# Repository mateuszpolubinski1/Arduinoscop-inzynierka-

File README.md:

# ArduinoScope – Modular Educational Measurement Device
*A universal, low-cost measurement platform based on Raspberry Pi Pico*

---

## Overview
ArduinoScope is a **modular electronic measurement device** designed as an educational platform for electronics and metrology laboratories.  
The project was developed as an **engineering thesis** and combines **analog front-end design**, **ADC-based signal acquisition**, and **embedded software development**.

The device is built around the **Raspberry Pi Pico (RP2040)** microcontroller and can be reconfigured via software to operate as:
- Oscilloscope
- Spectrum analyzer
- Wobuloscope
- Vector voltmeter
- Frequency counter

---

## System Architecture
The system is based on a **modular architecture**, consisting of a mainboard and multiple plug-in expansion modules.

Key blocks of the system:
- Modular analog input boards
- Mainboard with Raspberry Pi Pico (RP2040)
- Internal ADC for signal acquisition
- TFT display with touchscreen
- USB interface for communication with a PC
- Dedicated power supply module

---

## Analog Front-End Design
Two independent analog input paths were designed to support different measurement scenarios.

### Differential Input Path

- Based on **INA2137 instrumentation amplifier**
- Fixed gain using precision, internally matched resistors
- High common-mode rejection (CMRR)
- Enables voltage measurement between any two points in a circuit
- Dedicated overvoltage protection to protect the ADC

---

### Single-Ended Input Path

- Based on **OPA1644 / TL084 operational amplifiers**
- Electronically adjustable gain
- Separate signal paths for DC and AC components
- Software-controlled signal conditioning similar to a classic oscilloscope
- Input and output protection for safe educational use

---

## Protection & Signal Conditioning
To ensure robustness and safe operation:
- Input protection using **BAV99-AQ diodes** (low leakage, low capacitance)
- ADC protection using **BAS40 Schottky diodes**
- Precision voltage references (**TL431**, **LM385**) for proper ADC range adaptation
- Designed to withstand accidental overvoltage conditions during laboratory exercises

---

## PCB Design
Custom printed circuit boards were designed using **KiCad**, with particular attention to analog signal integrity.

PCB design highlights:
- Modular plug-in boards connected via pin headers
- Noise-aware routing and ground plane usage
- Separation of analog and digital sections
- Easy manufacturing and repair

---

## Software
The firmware was developed using:
- **Arduino**
- **MicroPython**

Main software features:
- Data acquisition from internal ADC
- Signal processing and scaling
- User interface handling (display and touchscreen)
- USB communication for offline data transfer to PC

---

## Measurements & Validation
The device was validated through laboratory measurements.

Validation results:
- Correct operation within the acoustic frequency range
- Stable gain and offset control
- Proper operation of protection circuits
- Reliable signal acquisition using the RP2040 ADC

---

## User Interface
The built-in TFT display provides direct visualization of measured signals.

The user interface allows real-time interaction and configuration without the need for an external computer.

---

## Technologies Used
**Hardware**
- Raspberry Pi Pico (RP2040)
- INA2137, OPA1644, TL084
- AD9850 signal generator
- PCF8575 I/O expander

**Software & Tools**
- Arduino, MicroPython
- KiCad, LTspice
- Oscilloscope and laboratory measurement equipment

---

## Project Status & Future Work
Status:
- Fully functional prototype
- Successfully tested in laboratory conditions

Possible future improvements:
- External higher-resolution ADC
- Improved bandwidth and noise performance
- PC-based visualization and analysis software

---

## Author
**Mateusz Połubiński**  
Electronics Engineering – Warsaw University of Technology

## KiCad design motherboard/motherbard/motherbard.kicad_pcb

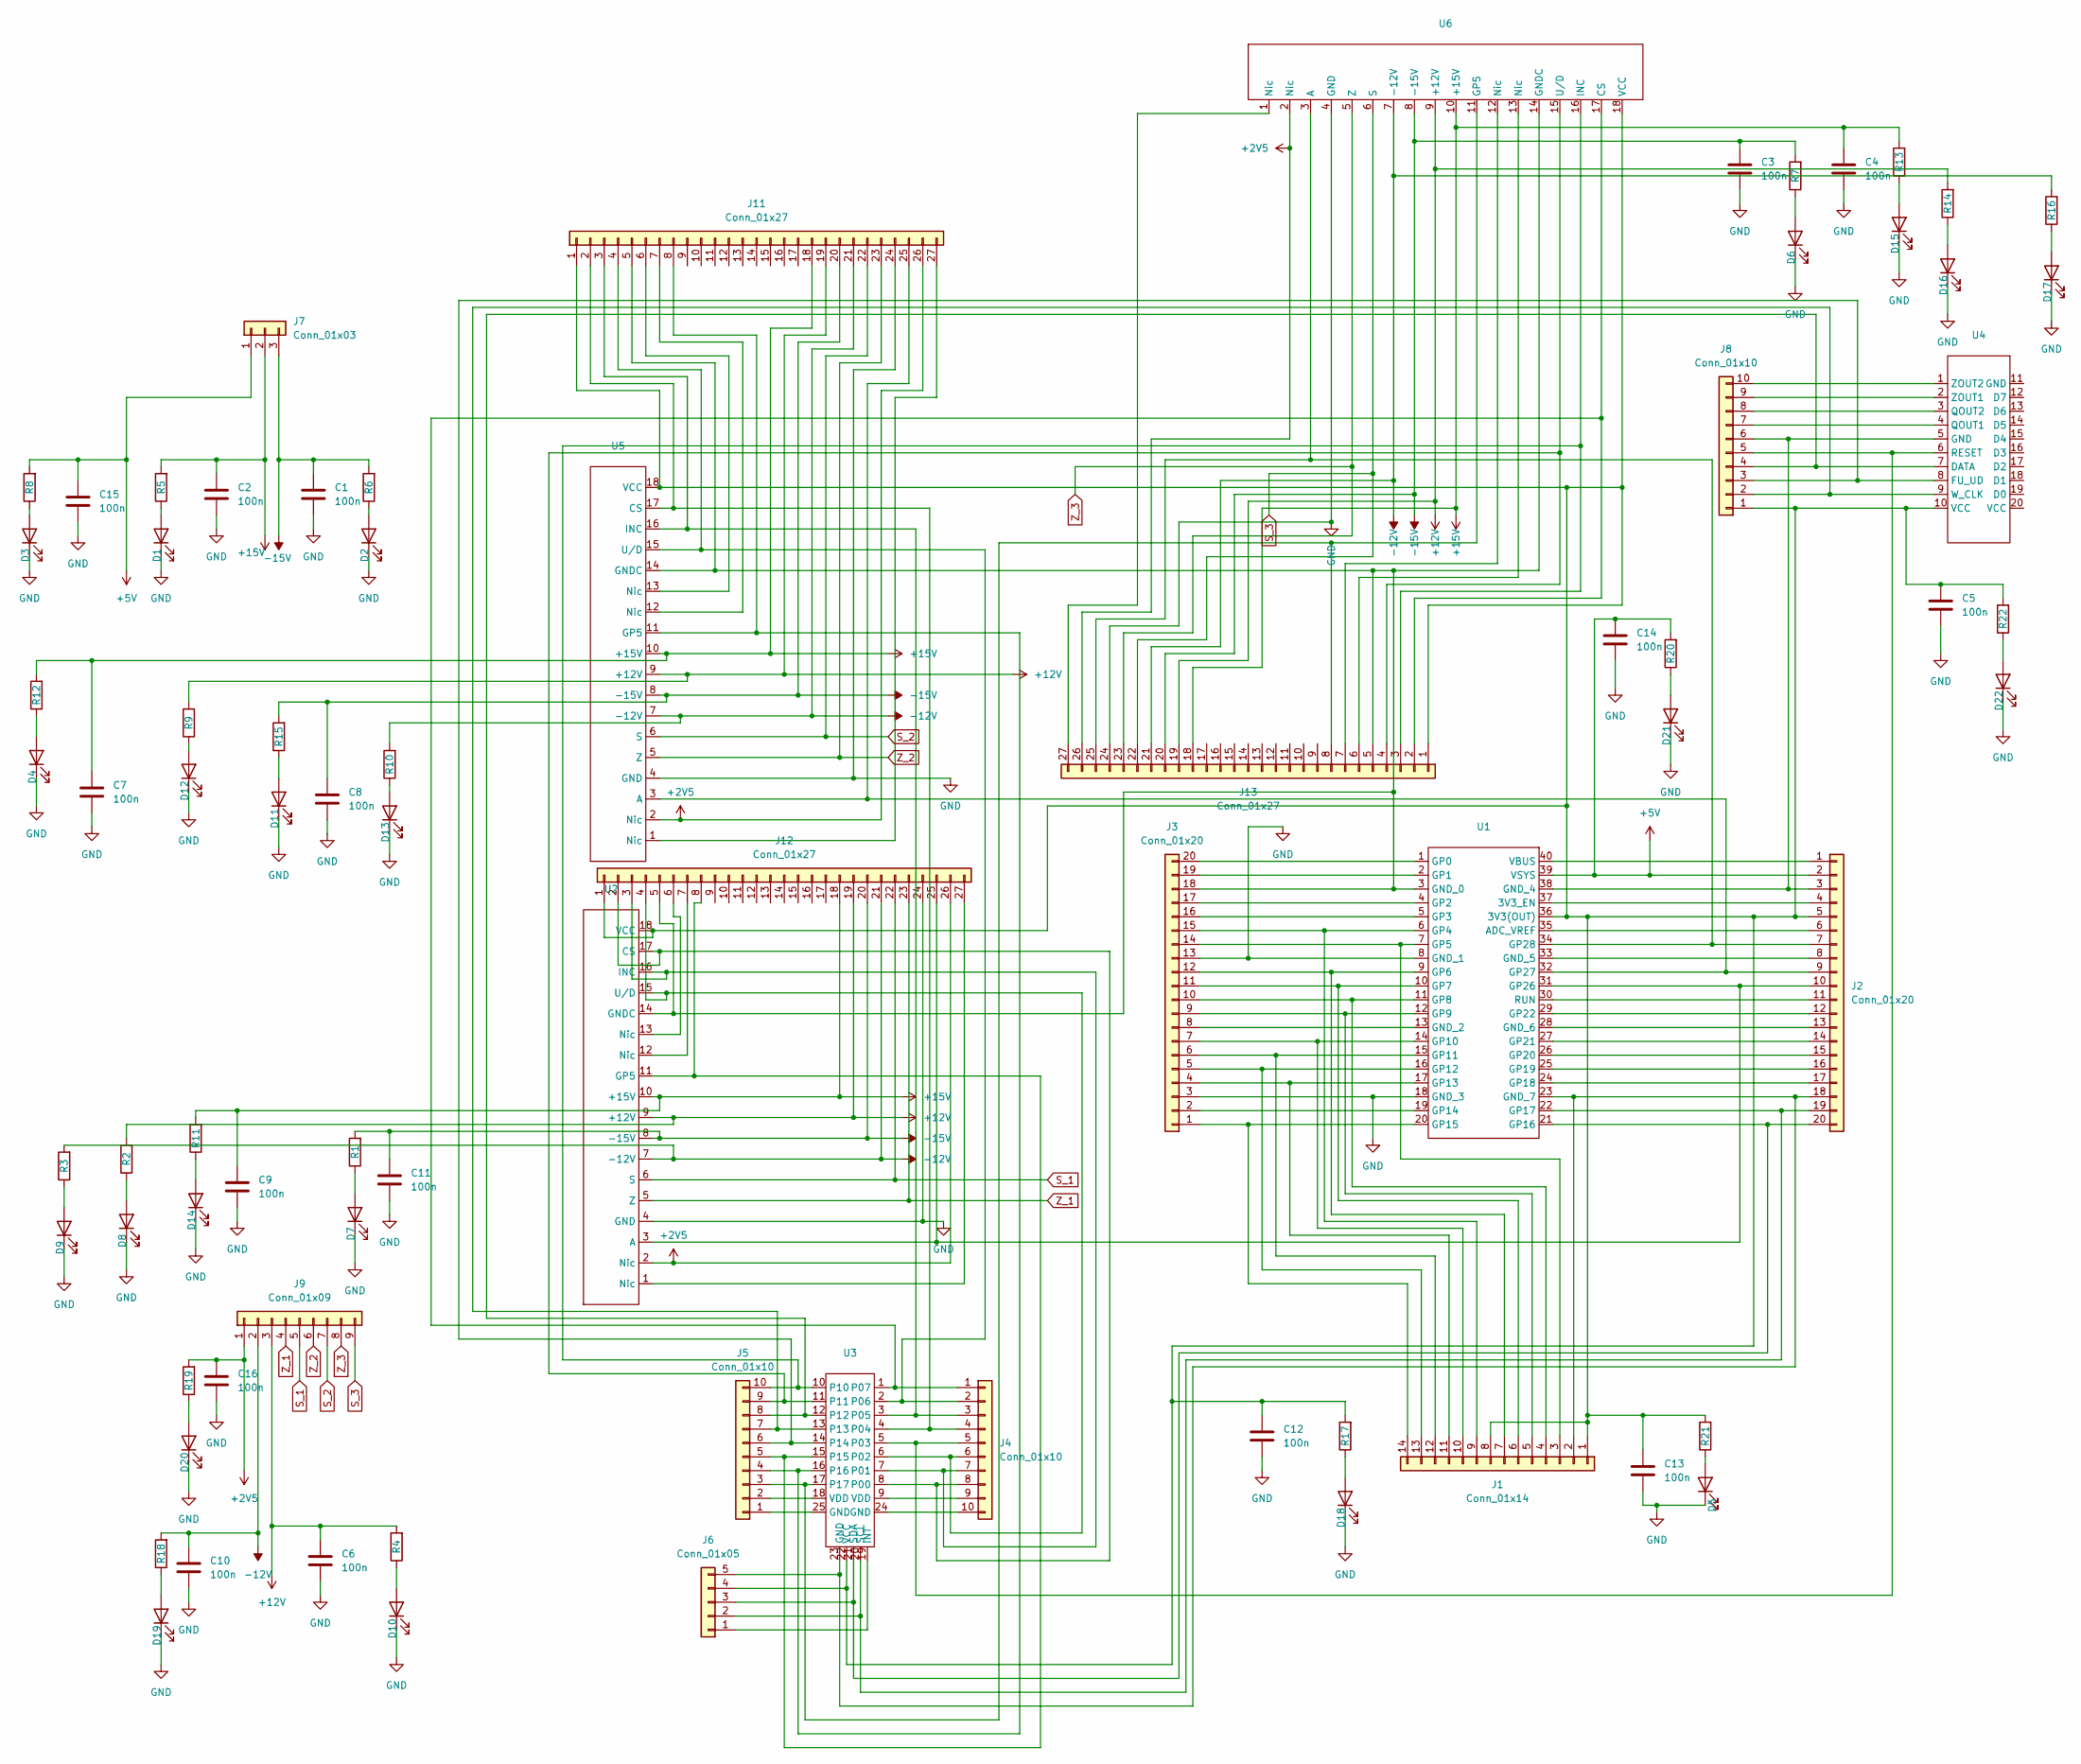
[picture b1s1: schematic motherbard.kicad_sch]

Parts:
C1, C2, C3, C4, C5, C6, C7, C8, C9, C10, C11, C12, C13, C14, C15, C16: 100n; C_1206_3216Metric_Pad1.33x1.80mm_HandSolder
D1, D2, D3, D4, D5, D6, D7, D8, D9, D10, D11, D12, D13, D14, D15, D16, D17, D18, D19, D20, D21, D22: IR26-21C_L110_TR8; LED_1206_3216Metric
J1: Conn_01x14; PinSocket_1x14_P2.54mm_Vertical
J2, J3: Conn_01x20; PinSocket_1x20_P2.54mm_Vertical
J4, J5, J8: Conn_01x10; PinHeader_1x10_P2.54mm_Vertical
J6: Conn_01x05; PinHeader_1x05_P2.54mm_Vertical
J7: Conn_01x03; PinHeader_1x03_P2.54mm_Vertical
J9: Conn_01x09; PinHeader_1x09_P2.54mm_Vertical
J11, J12, J13: Conn_01x27; PinSocket_1x27_P2.54mm_Vertical
R1, R2, R3, R4, R5, R6, R7, R8, R9, R10, R11, R12, R13, R14, R15, R16, R17, R18, R19, R20, R21, R22: R; R_1206_3216Metric_Pad1.30x1.75mm_HandSolder
U1: raspberry pi pico
U2, U5, U6: płytka
U3: ekspander
U4: generator

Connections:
+2V5: C16.1, J9.1, J11.26, J12.26, J13.26, R19.2, U2.2 (Nic), U5.2 (Nic), U6.2 (Nic)
+5V: C14.1, C15.1, J2.2, J7.1, R8.2, R20.2, U1.39 (VSYS)
+12V: C6.1, J9.3, J11.19, J12.19, J13.19, R2.2, R4.2, R9.2, R14.2, U2.9 (+12V), U5.9 (+12V), U6.9 (+12V)
+15V: C2.1, C4.1, C7.1, C9.1, J7.2, J11.18, J12.18, J13.18, R5.2, R11.2, R12.2, R13.2, U2.10 (+15V), U5.10 (+15V), U6.10 (+15V)
-12V: C10.1, J9.2, J11.21, J12.21, J13.21, R3.2, R10.2, R16.2, R18.2, U2.7 (-12V), U5.7 (-12V), U6.7 (-12V)
-15V: C1.1, C3.1, C8.1, C11.1, J7.3, J11.20, J12.20, J13.20, R1.2, R6.2, R7.2, R15.2, U2.8 (-15V), U5.8 (-15V), U6.8 (-15V)
GND: C1.2, C2.2, C3.2, C4.2, C5.2, C6.2, C7.2, C8.2, C9.2, C10.2, C11.2, C12.2, C13.2, C14.2, C15.2, C16.2, D1.1 (K), D2.1 (K), D3.1 (K), D4.1 (K), D5.1 (K), D6.1 (K), D7.1 (K), D8.1 (K), D9.1 (K), D10.1 (K), D11.1 (K), D12.1 (K), D13.1 (K), D14.1 (K), D15.1 (K), D16.1 (K), D17.1 (K), D18.1 (K), D19.1 (K), D20.1 (K), D21.1 (K), D22.1 (K), J3.3, J3.13, J11.24, J12.24, J13.24, U1.8 (GND_1), U1.18 (GND_3), U2.4 (GND), U5.4 (GND), U6.4 (GND)
unnamed: D1.2 (A), R5.1
unnamed: D2.2 (A), R6.1
unnamed: D3.2 (A), R8.1
unnamed: D4.2 (A), R12.1
unnamed: D5.2 (A), R21.1
unnamed: D6.2 (A), R7.1
unnamed: D7.2 (A), R1.1
unnamed: D8.2 (A), R2.1
unnamed: D9.2 (A), R3.1
unnamed: D10.2 (A), R4.1
unnamed: D11.2 (A), R15.1
unnamed: D12.2 (A), R9.1
unnamed: D13.2 (A), R10.1
unnamed: D14.2 (A), R11.1
unnamed: D15.2 (A), R13.1
unnamed: D16.2 (A), R14.1
unnamed: D17.2 (A), R16.1
unnamed: D18.2 (A), R17.1
unnamed: D19.2 (A), R18.1
unnamed: D20.2 (A), R19.1
unnamed: D21.2 (A), R20.1
unnamed: D22.2 (A), R22.1
unnamed: C5.1, C12.1, C13.1, J1.1, J1.8, J2.5, J6.4, J8.1, J11.1, J12.1, J13.1, R17.2, R21.2, R22.2, U1.36 (3V3(OUT)), U2.18 (VCC), U3.22 (VCC), U4.10 (VCC), U5.18 (VCC), U6.18 (VCC)
unnamed: J1.2, J2.18, J6.5, U1.23 (GND_7), U3.23 (GND)
unnamed: J1.3, J3.14, U1.7 (GP5)
unnamed: J1.4, J3.10, U1.11 (GP8)
unnamed: J1.5, J3.9, U1.12 (GP9)
unnamed: J1.6, J3.11, U1.10 (GP7)
unnamed: J1.7, J3.12, U1.9 (GP6)
unnamed: J1.9, J3.15, U1.6 (GP4)
unnamed: J1.10, J3.7, U1.14 (GP10)
unnamed: J1.11, J3.4, U1.17 (GP13)
unnamed: J1.12, J3.6, U1.15 (GP11)
unnamed: J1.13, J3.5, U1.16 (GP12)
unnamed: J1.14, J3.1, U1.20 (GP15)
unnamed: J2.1, U1.40 (VBUS)
unnamed: J2.3, J8.6, U1.38 (GND_4), U4.5 (GND)
unnamed: J2.4, U1.37 (3V3_EN)
unnamed: J2.6, U1.35 (ADC_VREF)
unnamed: J2.8, U1.33 (GND_5)
unnamed: J2.11, U1.30 (RUN)
unnamed: J2.12, U1.29 (GP22)
unnamed: J2.13, U1.28 (GND_6)
unnamed: J2.14, U1.27 (GP21)
unnamed: J2.15, U1.26 (GP20)
unnamed: J2.16, U1.25 (GP19)
unnamed: J2.17, U1.24 (GP18)
unnamed: J2.19, J6.2, U1.22 (GP17), U3.20 (SCL)
unnamed: J2.20, J6.3, U1.21 (GP16), U3.21 (SDA)
unnamed: J3.2, U1.19 (GP14)
unnamed: J3.8, U1.13 (GND_2)
unnamed: J3.16, U1.5 (GP3)
unnamed: J3.17, U1.4 (GP2)
unnamed: J3.19, U1.2 (GP1)
unnamed: J3.20, U1.1 (GP0)
unnamed: J4.5, J8.5, U3.5 (P03), U4.6 (RESET)
unnamed: J4.9, U3.9 (VDD)
unnamed: J4.10, U3.24 (GND)
unnamed: J5.1, U3.25 (GND)
unnamed: J5.2, U3.18 (VDD)
unnamed: J5.6, J8.3, U3.14, U4.8 (FU_UD)
unnamed: J5.7, J8.2, U3.13, U4.9 (W_CLK)
unnamed: J5.8, J8.4, U3.12, U4.7 (DATA)
unnamed: J6.1, U3.19 (INT)
unnamed: J8.7, U4.4 (QOUT1)
unnamed: J8.8, U4.3 (QOUT2)
unnamed: J8.9, U4.2 (ZOUT1)
unnamed: J8.10, U4.1 (ZOUT2)
unnamed: J4.4, J11.2, U3.4, U5.17 (CS)
unnamed: J4.3, J11.3, U3.3 (P05), U5.16 (INC)
unnamed: J4.2, J11.4, U3.2 (P06), U5.15 (U/D)
unnamed: J3.18, J11.5, J12.5, J13.5, U1.3 (GND_0), U2.14 (GNDC), U5.14 (GNDC), U6.14 (GNDC)
unnamed: J11.6, U5.13 (Nic)
unnamed: J11.7, U5.12 (Nic)
unnamed: J5.4, J11.8, U3.16, U5.11 (GP5)
unnamed: J2.9, J11.25, U1.32 (GP27), U5.3 (A)
unnamed: J11.27, U5.1 (Nic)
unnamed: J4.8, J12.2, U2.17 (CS), U3.8 (P00)
unnamed: J4.7, J12.3, U2.16 (INC), U3.7 (P01)
unnamed: J4.6, J12.4, U2.15 (U/D), U3.6 (P02)
unnamed: J12.6, U2.13 (Nic)
unnamed: J12.7, U2.12 (Nic)
unnamed: J5.5, J12.8, U2.11 (GP5), U3.15
unnamed: J2.10, J12.25, U1.31 (GP26), U2.3 (A)
unnamed: J12.27, U2.1 (Nic)
unnamed: J4.1, J13.2, U3.1 (P07), U6.17 (CS)
unnamed: J5.10, J13.3, U3.10, U6.16 (INC)
unnamed: J5.9, J13.4, U3.11, U6.15 (U/D)
unnamed: J13.6, U6.13 (Nic)
unnamed: J13.7, U6.12 (Nic)
unnamed: J5.3, J13.8, U3.17, U6.11 (GP5)
unnamed: J2.7, J13.25, U1.34 (GP28), U6.3 (A)
unnamed: J13.27, U6.1 (Nic)
S_1: J9.5, J12.22, U2.6 (S)
S_2: J9.7, J11.22, U5.6 (S)
S_3: J9.9, J13.22, U6.6 (S)
Z_1: J9.4, J12.23, U2.5 (Z)
Z_2: J9.6, J11.23, U5.5 (Z)
Z_3: J9.8, J13.23, U6.5 (Z)

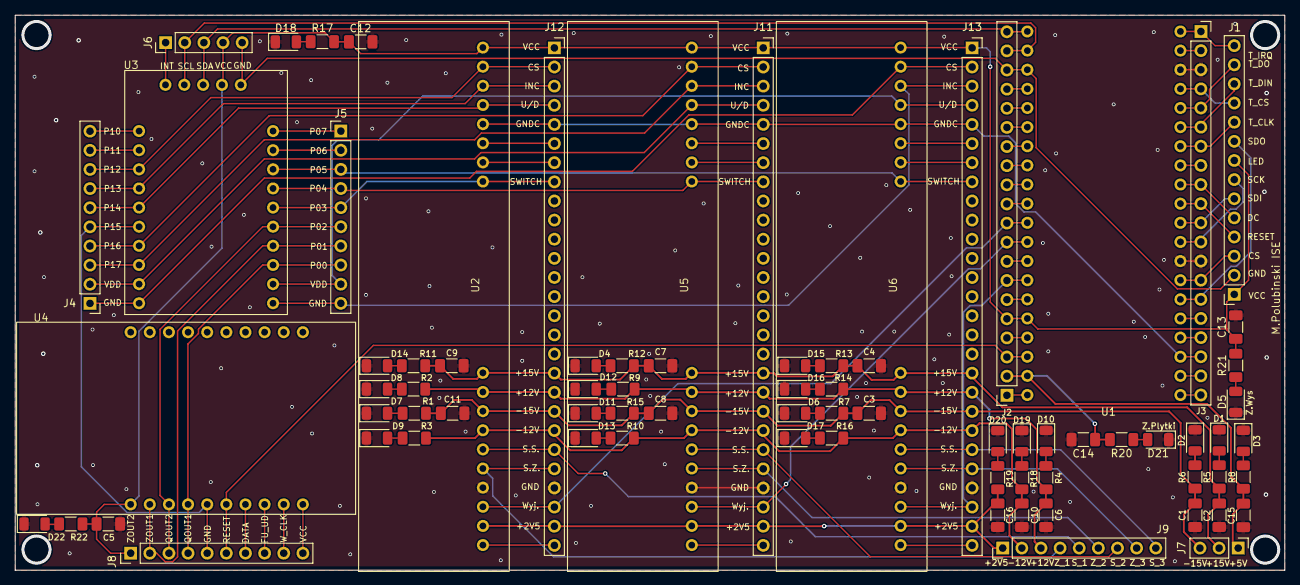
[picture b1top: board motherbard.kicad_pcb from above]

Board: 2 copper layers, 168.5 x 73.7 mm, 78 parts (0 on the bottom side), 106 nets.

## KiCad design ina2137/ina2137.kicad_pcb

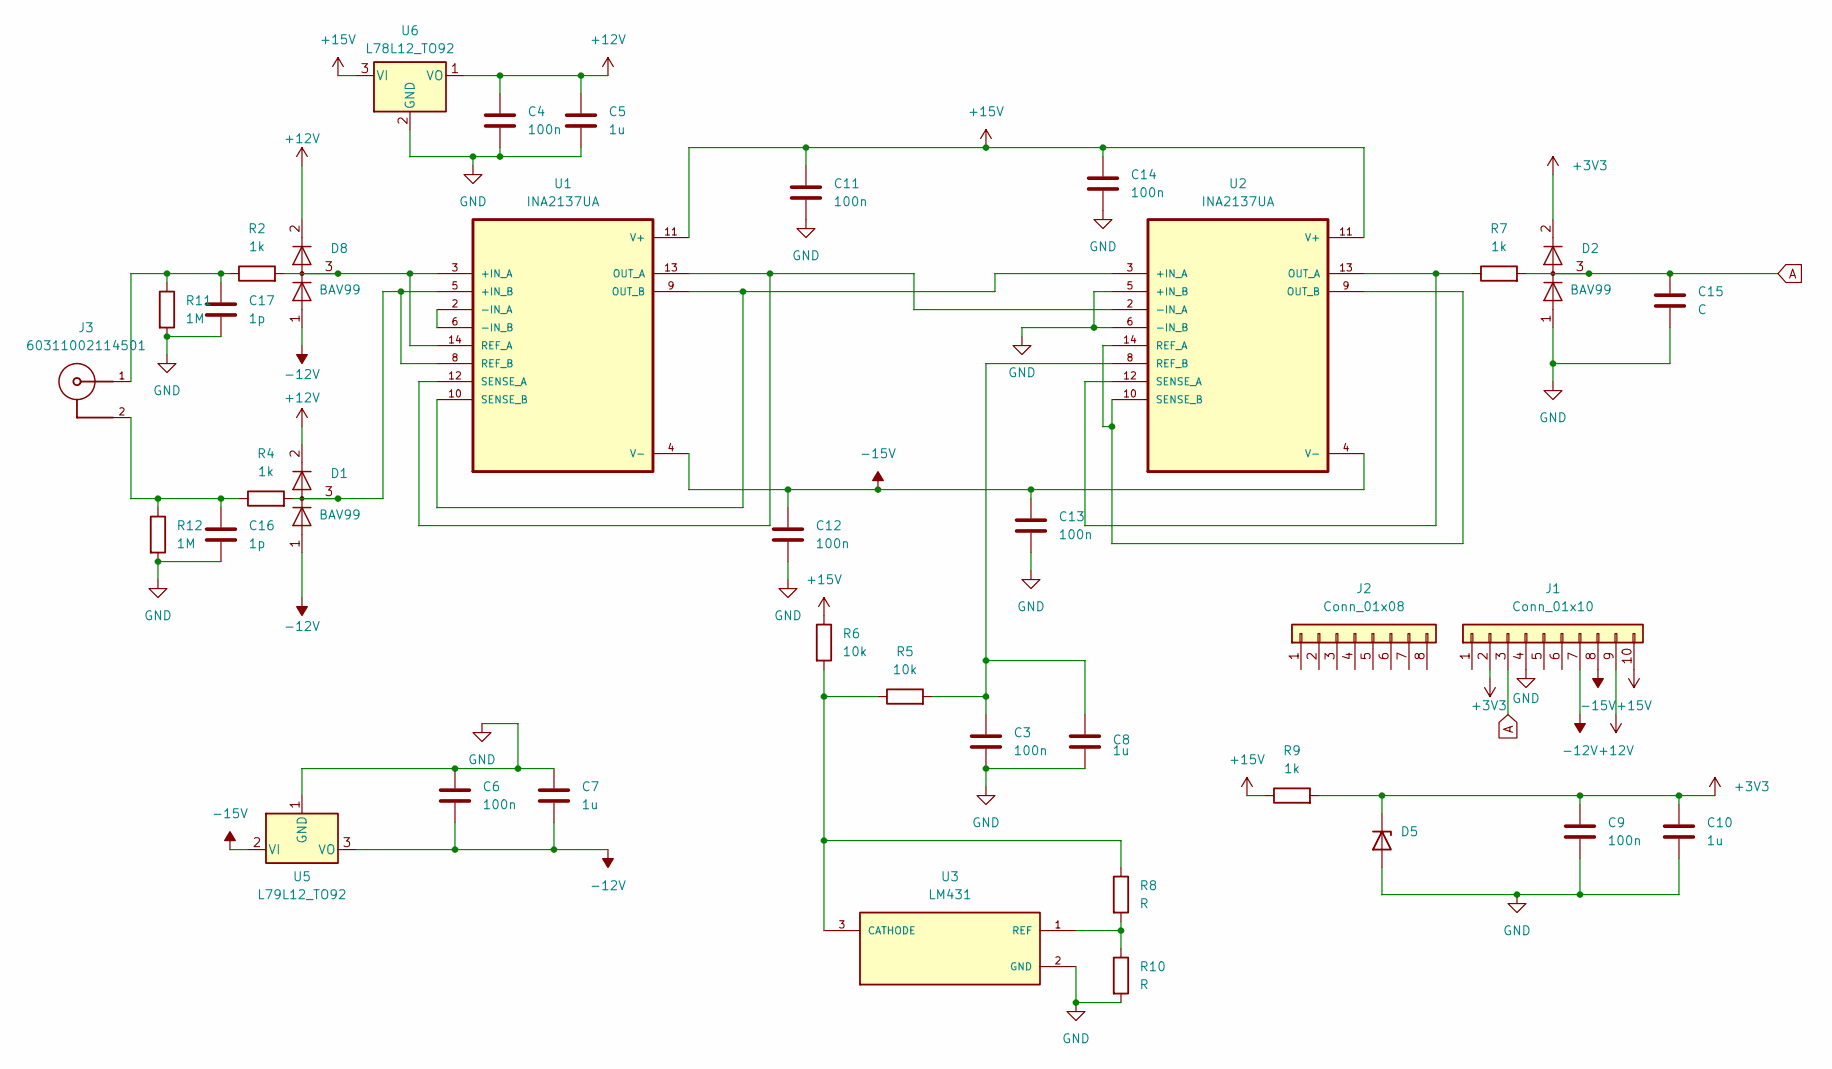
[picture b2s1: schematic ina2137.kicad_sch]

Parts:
C3, C4, C6, C9, C11, C12, C13, C14: 100n; C_1206_3216Metric_Pad1.33x1.80mm_HandSolder
C5, C7, C8, C10: 1u; CP_Radial_Tantal_D7.0mm_P5.00mm
C15: C; C_1206_3216Metric_Pad1.33x1.80mm_HandSolder
C16, C17: 1p; C_1206_3216Metric_Pad1.33x1.80mm_HandSolder
D1, D2, D8: BAV99; SOT-23
D5: D_A-405_P2.54mm_Vertical_KathodeUp
J1: Conn_01x10; PinHeader_1x10_P2.54mm_Vertical
J2: Conn_01x08; PinHeader_1x08_P2.54mm_Vertical
J3: 60311002114501; SMA_Molex_73251-2200_Horizontal; PART-NUMBER 60311002114501
R2, R4, R7, R9: 1k; R_1206_3216Metric_Pad1.30x1.75mm_HandSolder
R5, R6: 10k; R_1206_3216Metric_Pad1.30x1.75mm_HandSolder
R8, R10: R; R_1206_3216Metric_Pad1.30x1.75mm_HandSolder
R11, R12: 1M; R_1206_3216Metric_Pad1.30x1.75mm_HandSolder
U1, U2: INA2137UA; SOIC127P600X175-14N
U3: LM431; TO-92
U5: L79L12_TO92; TO-92_Inline
U6: L78L12_TO92; TO-92_Inline

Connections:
+3V3: C9.1, C10.1, D2.2 (A), D5.1 (K), J1.2, R9.2
+12V: C4.1, C5.1, D1.2 (A), D8.2 (A), J1.9, U6.1 (VO)
+15V: C11.1, C14.1, J1.10, R6.1, R9.1, U1.11 (V+), U2.11 (V+), U6.3 (VI)
-12V: C6.2, C7.2, D1.1 (K), D8.1 (K), J1.7, U5.3 (VO)
-15V: C12.1, C13.1, J1.8, U1.4 (V-), U2.4 (V-), U5.2 (VI)
A: C15.1, D2.3 (K), J1.3, R7.2
GND: C3.2, C4.2, C5.2, C6.1, C7.1, C8.2, C9.2, C10.2, C11.2, C12.2, C13.2, C14.2, C15.2, C16.2, C17.2, D2.1 (K), D5.2 (A), J1.4, R10.2, R11.2, R12.2, U2.5 (+IN_B), U2.6 (-IN_B), U3.2 (GND), U5.1 (GND), U6.2 (GND)
unnamed: C16.1, J3.2, R4.1, R12.1
unnamed: C17.1, J3.1, R2.1, R11.1
unnamed: D8.3 (K), R2.2, U1.3 (+IN_A), U1.14 (REF_A)
unnamed: D1.3 (K), R4.2, U1.5 (+IN_B), U1.8 (REF_B)
unnamed: U1.2 (-IN_A), U1.6 (-IN_B)
unnamed: U1.12 (SENSE_A), U1.13 (OUT_A), U2.2 (-IN_A)
unnamed: U1.9 (OUT_B), U1.10 (SENSE_B), U2.3 (+IN_A)
unnamed: R7.1, U2.12 (SENSE_A), U2.13 (OUT_A)
unnamed: U2.9 (OUT_B), U2.10 (SENSE_B), U2.14 (REF_A)
unnamed: C3.1, C8.1, R5.2, U2.8 (REF_B)
unnamed: R5.1, R6.2, R8.1, U3.3 (CATHODE)
unnamed: R8.2, R10.1, U3.1 (REF)

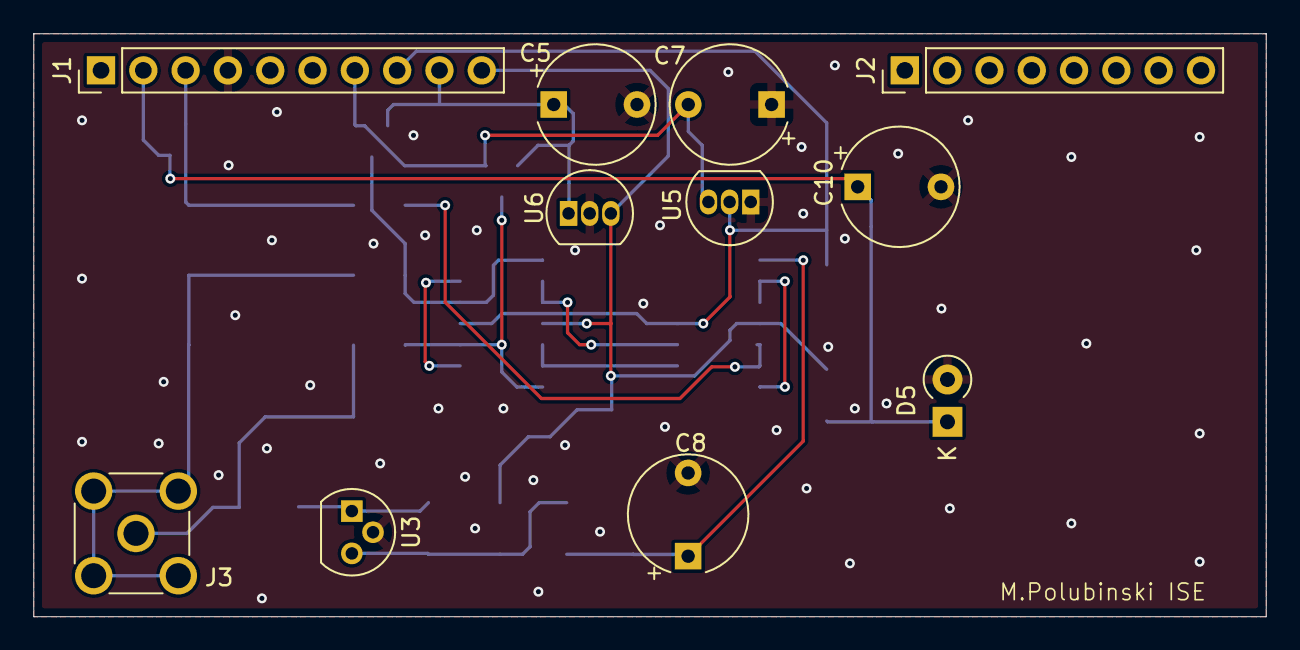
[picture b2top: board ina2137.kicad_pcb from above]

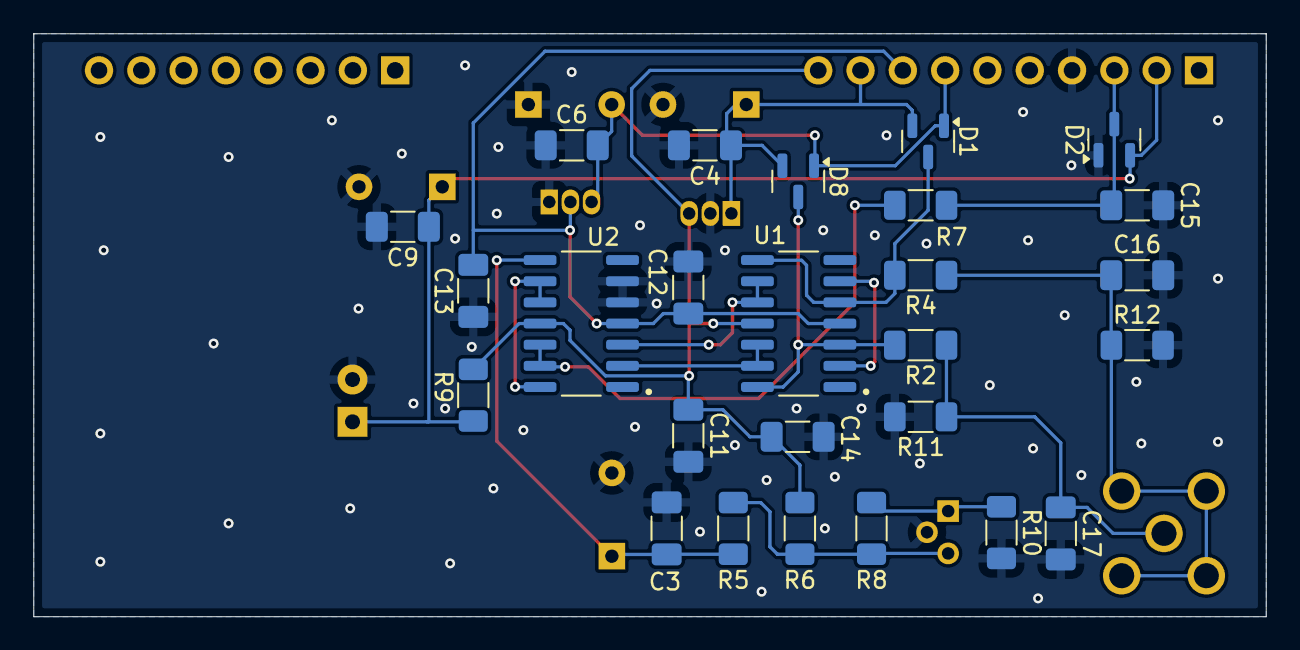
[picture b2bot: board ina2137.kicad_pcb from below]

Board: 2 copper layers, 74.0 x 35.0 mm, 37 parts (26 on the bottom side), 19 nets.

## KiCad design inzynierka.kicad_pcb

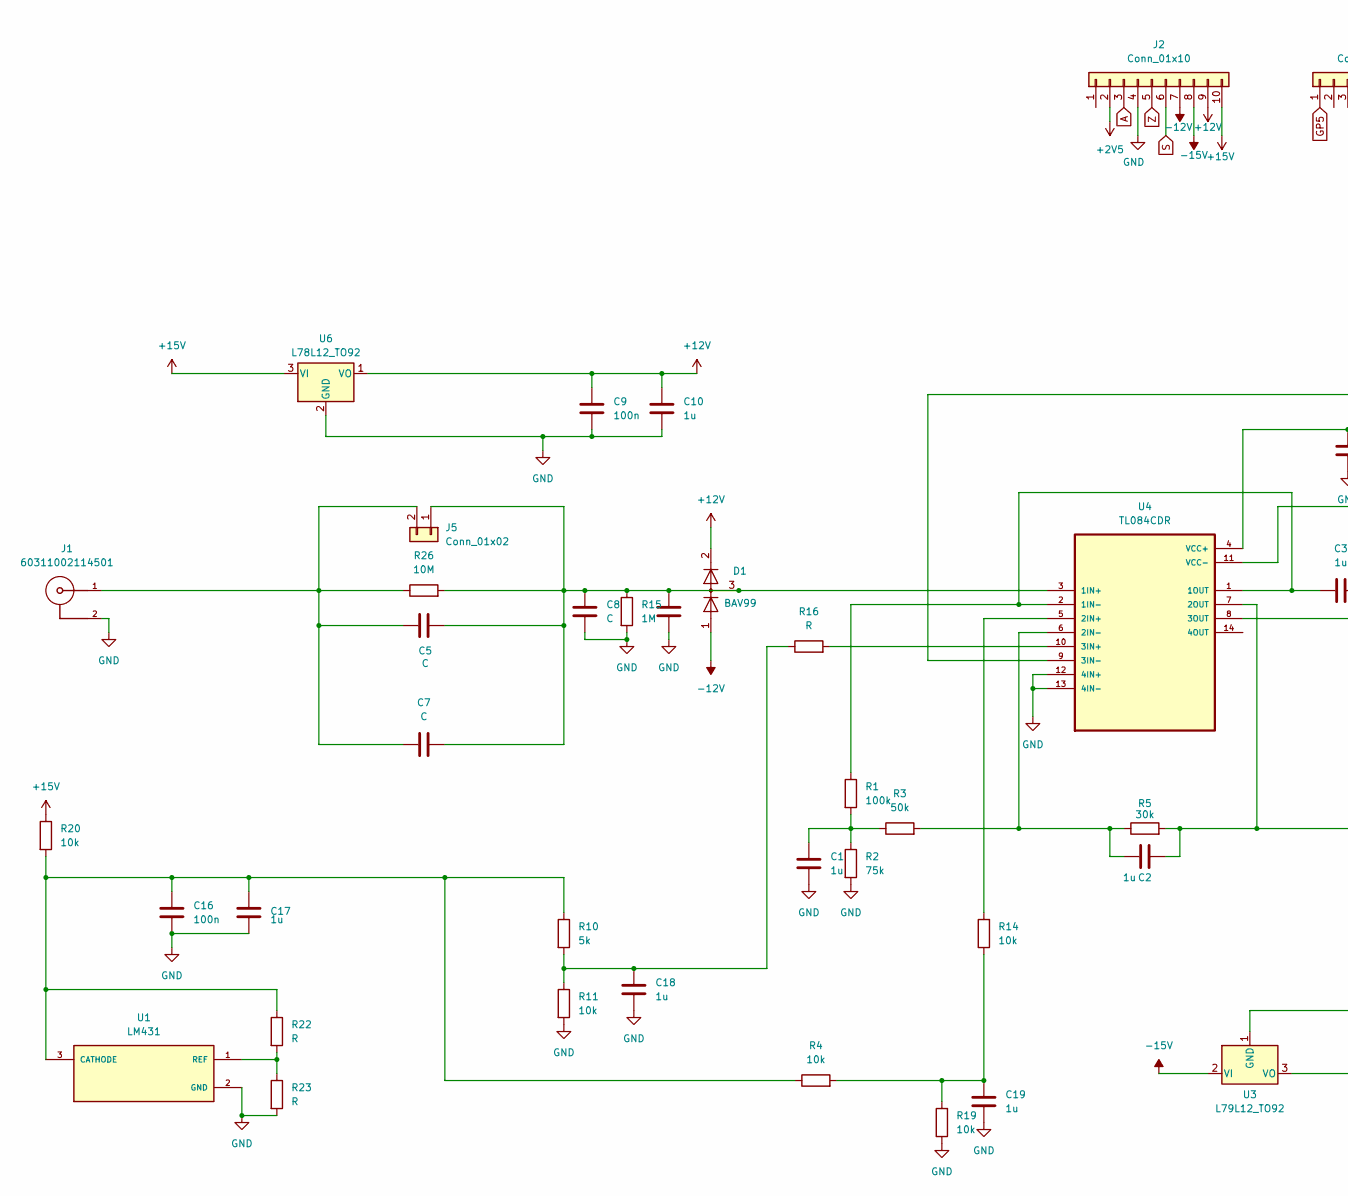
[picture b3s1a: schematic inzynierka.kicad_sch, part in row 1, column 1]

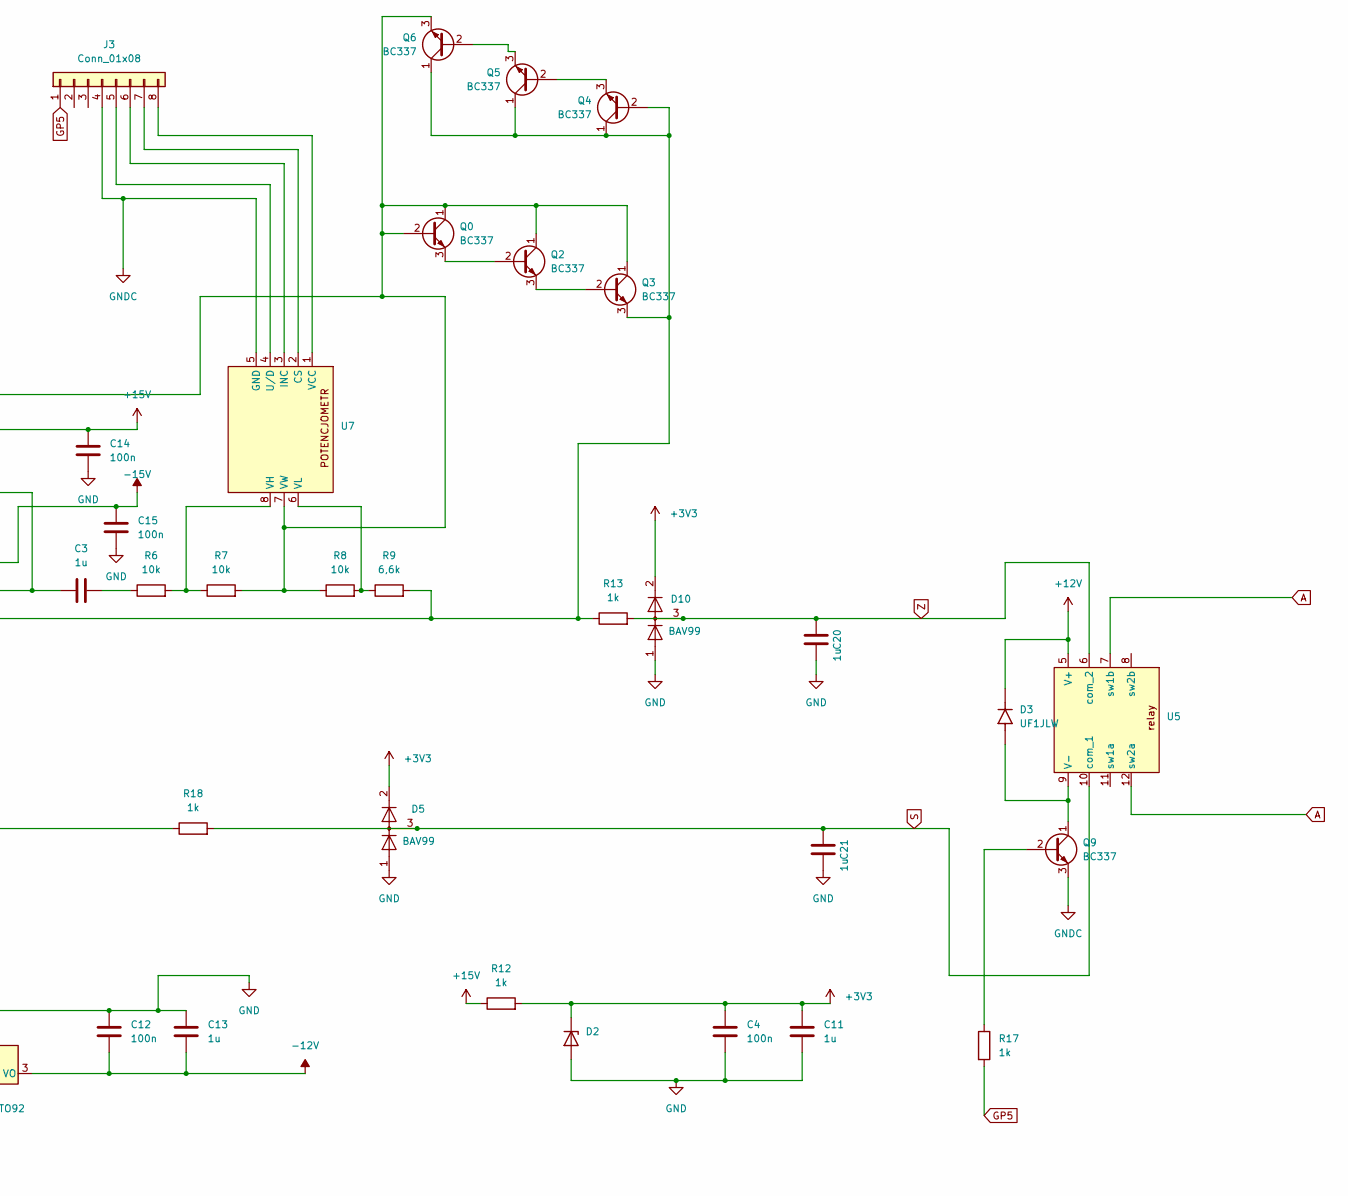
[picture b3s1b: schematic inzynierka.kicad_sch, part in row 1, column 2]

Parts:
C1, C2, C3: 1u; C_1206_3216Metric
C4, C9, C12, C14, C15: 100n; C_1206_3216Metric
C5, C6, C8: C; C_1206_3216Metric
C7: C; CP_Radial_Tantal_D5.5mm_P5.00mm
C10, C11, C13, C17: 1u; CP_Radial_Tantal_D7.0mm_P5.00mm
C16: 100n; C_1206_3216Metric_Pad1.33x1.80mm_HandSolder
C18, C19, C20, C21: 1u; C_1206_3216Metric_Pad1.33x1.80mm_HandSolder
D1, D5, D10: BAV99; SOT-23
D2: D_A-405_P2.54mm_Vertical_KathodeUp
D3: UF1JLW; SODFL3718X102N; PARTREV C2103
J1: 60311002114501; SMA_Molex_73251-2200_Horizontal; PART-NUMBER 60311002114501
J2: Conn_01x10; PinHeader_1x10_P2.54mm_Vertical
J3: Conn_01x08; PinHeader_1x08_P2.54mm_Vertical
J5: Conn_01x02; PinHeader_1x02_P2.54mm_Vertical
Q0, Q2, Q3, Q4, Q5, Q6, Q9: BC337; TO-92_Inline
R1: 100k; R_1206_3216Metric
R2: 75k; R_1206_3216Metric
R3: 50k; R_1206_3216Metric
R4, R6, R7, R8, R11, R14: 10k; R_1206_3216Metric
R5: 30k; R_1206_3216Metric
R9: 6,6k; R_1206_3216Metric
R10: 5k; R_1206_3216Metric
R12, R13, R17, R18: 1k; R_1206_3216Metric
R15: 1M; R_1206_3216Metric
R16, R22, R23: R; R_1206_3216Metric_Pad1.30x1.75mm_HandSolder
R19, R20: 10k; R_1206_3216Metric_Pad1.30x1.75mm_HandSolder
R26: 10M; R_1206_3216Metric
U1: LM431; TO-92
U3: L79L12_TO92; TO-92_Inline
U4: TL084CDR; SOIC127P600X175-14N
U5: relay
U6: L78L12_TO92; TO-92_Inline
U7: X9C1035 Digital Potentiometer

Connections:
+2V5: J2.2
+3V3: C4.1, C11.1, D2.1 (K), D5.2 (A), D10.2 (A), R12.2
+12V: C9.1, C10.1, D1.2 (A), D3.C, J2.9, U5.5 (V+), U6.1 (VO)
+15V: C14.1, J2.10, R12.1, R20.1, U4.4 (VCC+), U6.3 (VI)
-12V: C12.2, C13.2, D1.1 (K), J2.7, U3.3 (VO)
-15V: C15.1, J2.8, U3.2 (VI), U4.11 (VCC-)
A: J2.3, U5.7 (sw1b), U5.12 (sw2a)
GND: C1.2, C4.2, C6.2, C8.2, C9.2, C10.2, C11.2, C12.1, C13.1, C14.2, C15.2, C16.2, C17.2, C18.2, C19.2, C20.1, C21.1, D2.2 (A), D5.1 (K), D10.1 (K), J1.2, J2.4, R2.2, R11.2, R15.2, R19.1, R23.2, U1.2 (GND), U3.1 (GND), U4.12 (4IN+), U4.13 (4IN-), U6.2 (GND)
GNDC: J3.4, Q9.3 (E), U7.5 (GND)
GP5: J3.1, R17.2
unnamed: C1.1, R1.2, R2.1, R3.1
unnamed: C3.2, R6.1
unnamed: C18.1, R10.2, R11.1, R16.1
unnamed: C19.1, R4.2, R14.1, R19.2
unnamed: J3.5, U7.4 (U/D)
unnamed: J3.6, U7.3 (INC)
unnamed: J3.7, U7.2 (CS)
unnamed: J3.8, U7.1 (VCC)
unnamed: C5.2, C6.1, C7.1, C8.1, D1.3 (K), J5.1, R15.1, R26.2, U4.3 (1IN+)
unnamed: C5.1, C7.2, J1.1, J5.2, R26.1
unnamed: Q0.1 (C), Q0.2 (B), Q2.1 (C), Q3.1 (C), Q6.3 (E), R7.2, R8.1, U4.9 (3IN-), U7.7 (VW)
unnamed: Q0.3 (E), Q2.2 (B)
unnamed: Q2.3 (E), Q3.2 (B)
unnamed: Q3.3 (E), Q4.1 (C), Q4.2 (B), Q5.1 (C), Q6.1 (C), R9.2, R13.1, U4.8 (3OUT)
unnamed: Q4.3 (E), Q5.2 (B)
unnamed: Q5.3 (E), Q6.2 (B)
unnamed: Q9.2 (B), R17.1
unnamed: D3.A, Q9.1 (C), U5.9 (V-)
unnamed: C16.1, C17.1, R4.1, R10.1, R20.2, R22.1, U1.3 (CATHODE)
unnamed: R22.2, R23.1, U1.1 (REF)
unnamed: C3.1, R1.1, U4.1 (1OUT), U4.2 (1IN-)
unnamed: R14.2, U4.5 (2IN+)
unnamed: C2.1, R3.2, R5.1, U4.6 (2IN-)
unnamed: C2.2, R5.2, R18.1, U4.7 (2OUT)
unnamed: R16.2, U4.10 (3IN+)
unnamed: R6.2, R7.1, U7.8 (VH)
unnamed: R8.2, R9.1, U7.6 (VL)
S: C21.2, D5.3 (K), J2.6, R18.2, U5.10 (com_1)
Z: C20.2, D10.3 (K), J2.5, R13.2, U5.6 (com_2)

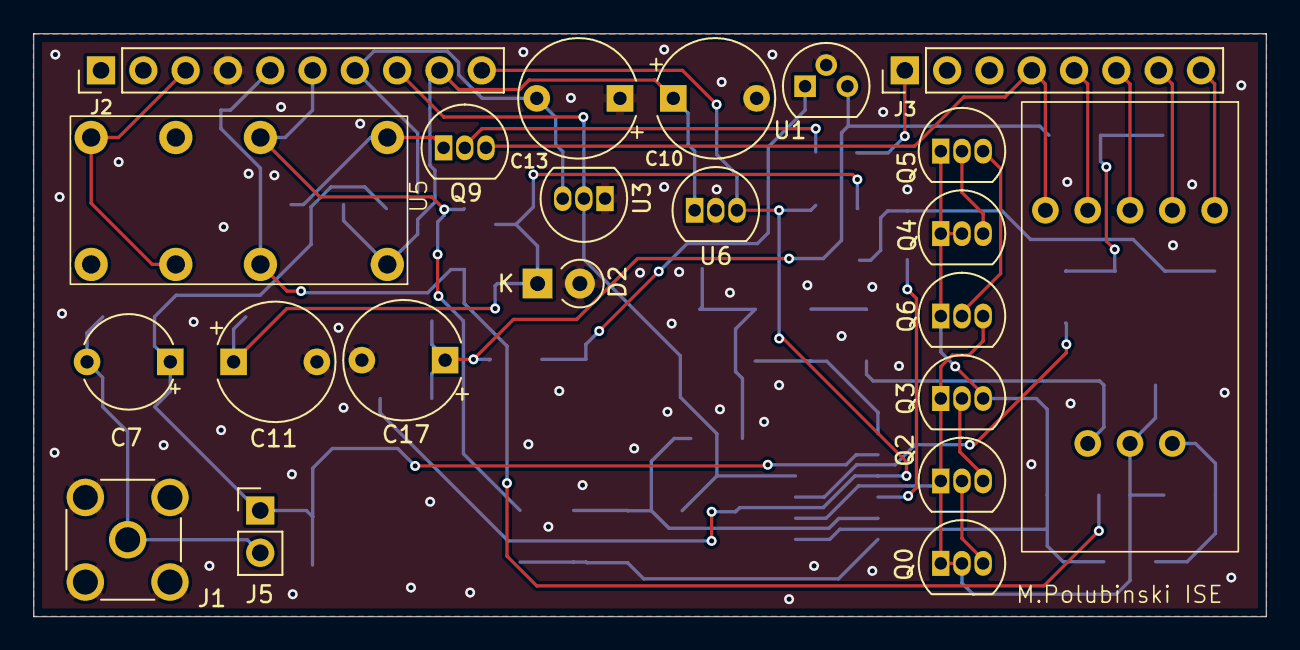
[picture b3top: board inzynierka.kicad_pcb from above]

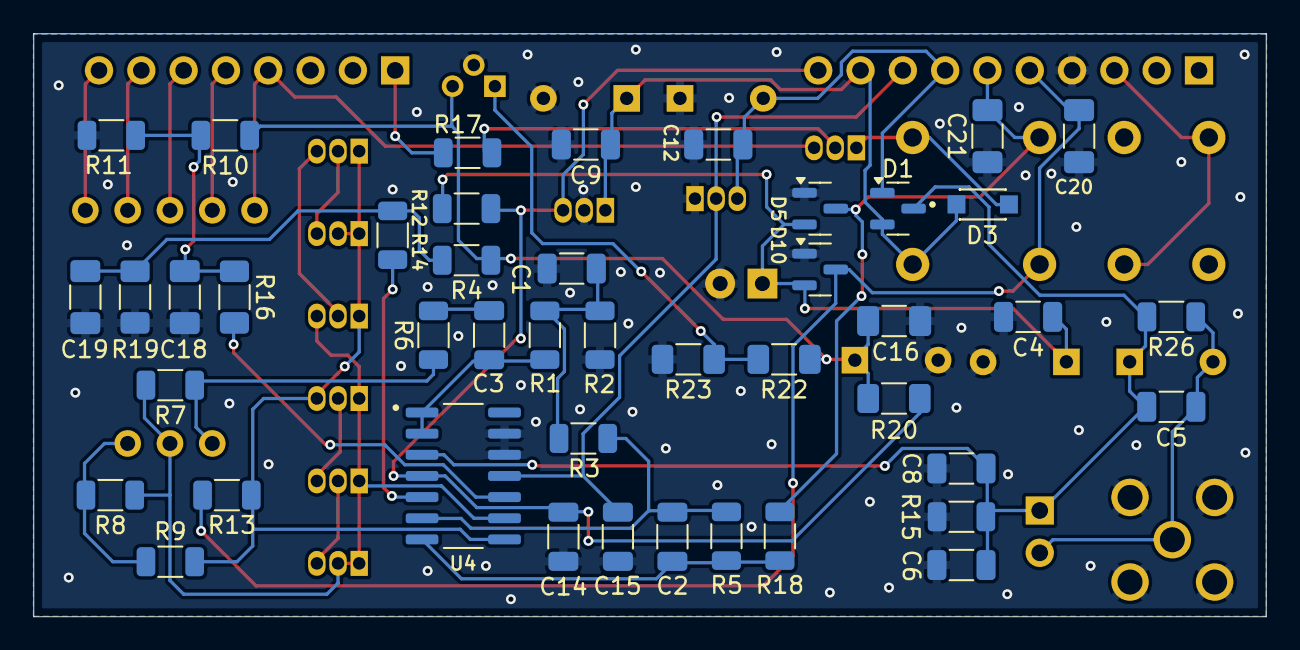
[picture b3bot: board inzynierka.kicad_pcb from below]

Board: 2 copper layers, 74.0 x 35.0 mm, 66 parts (44 on the bottom side), 38 nets.
